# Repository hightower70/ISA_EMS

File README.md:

# 2MByte ISA EMS Expansion Card for IBM PC XT computers

This is a redesign of the **lo-tech.co.uk** [2Mb ISA EMS board](https://www.lo-tech.co.uk/wiki/Lo-tech_2MB_EMS_Board) with some changes:

- All thru-hole instead of SMD, while retaining a rather compact format
- Simplified address decoding and storage circuits for less chip count

All design files and gerber files for PCB manufacturing are avaiable in the repository. The schematics [schematics](schematics.pdf) is also avaiable in PDF format.

The card was tested in modern replica of an XT computer like Xi8088 and Micro8088 without issues.

## Configuration

To configure the EMS, jumpers on J2 header are used.

Pins pairs 1 and 2 configure the Page Frame base address, while 3 and 4 configure the IO Port base address.

Page Frame Address:

| 1 | 2 | EMS Page Frame Base |
| - | - | ------------------- |
| X | X |        C000h        |
| - | X |        D000h        |
| X | - |        E000h        |
| - | - |       Invalid       |

Port Base Address

| 3 | 4 | EMS IO Port Base |
| - | - | ---------------- |
| X | X |     260-263h     |
| - | X |     264-267h     |
| X | - |     268-26Bh     |
| - | - |     26C-26Fh     |

 (-=no jumper (opened), X=jumper (closed))

## Usage

You need a **memory manager** to use this board. I'm including the `LTEMM` driver provided by lo-tech in this repository. Please refer to [this](https://www.lo-tech.co.uk/wiki/Terms_and_Conditions) page regarding the terms of use.

## Bill of Materials

All ICs are in DIP package.

- C1,C4 ,C5 ,C6, C7, C8, C9, C10, C11, C12: 100nF, ceramic
- C2, C3: 10uF / 50v electrolytic caps
- J2 2x4 2.5mm breakable header
- RN1: resistor network, 10k, bussed, 5 pins
- RN2: resistor network, 10k, bussed, 9 pins. 
- U1, U2, U3, U4: AS6C4008-55PCN (You don't need to fill all sockets: fit as much memory as you need starting from socket 1!)
- U5: 74LS139
- U6: 74LS245
- U7, U10: 74HCT688
- U8, U9: 74LS670
- ISA bracket: Keystone 9202, plus screws.

## Credits

- Thanks to [hkzab](https://github.com/hkzlab/ISA_EMS_2Mb) for publishing a similar design
- Thanks to [lo-tech.co.uk](https://www.lo-tech.co.uk/) for having published their schematics
- Thanks to [Sergey](http://www.malinov.com/Home/sergeys-projects) for all his projects!

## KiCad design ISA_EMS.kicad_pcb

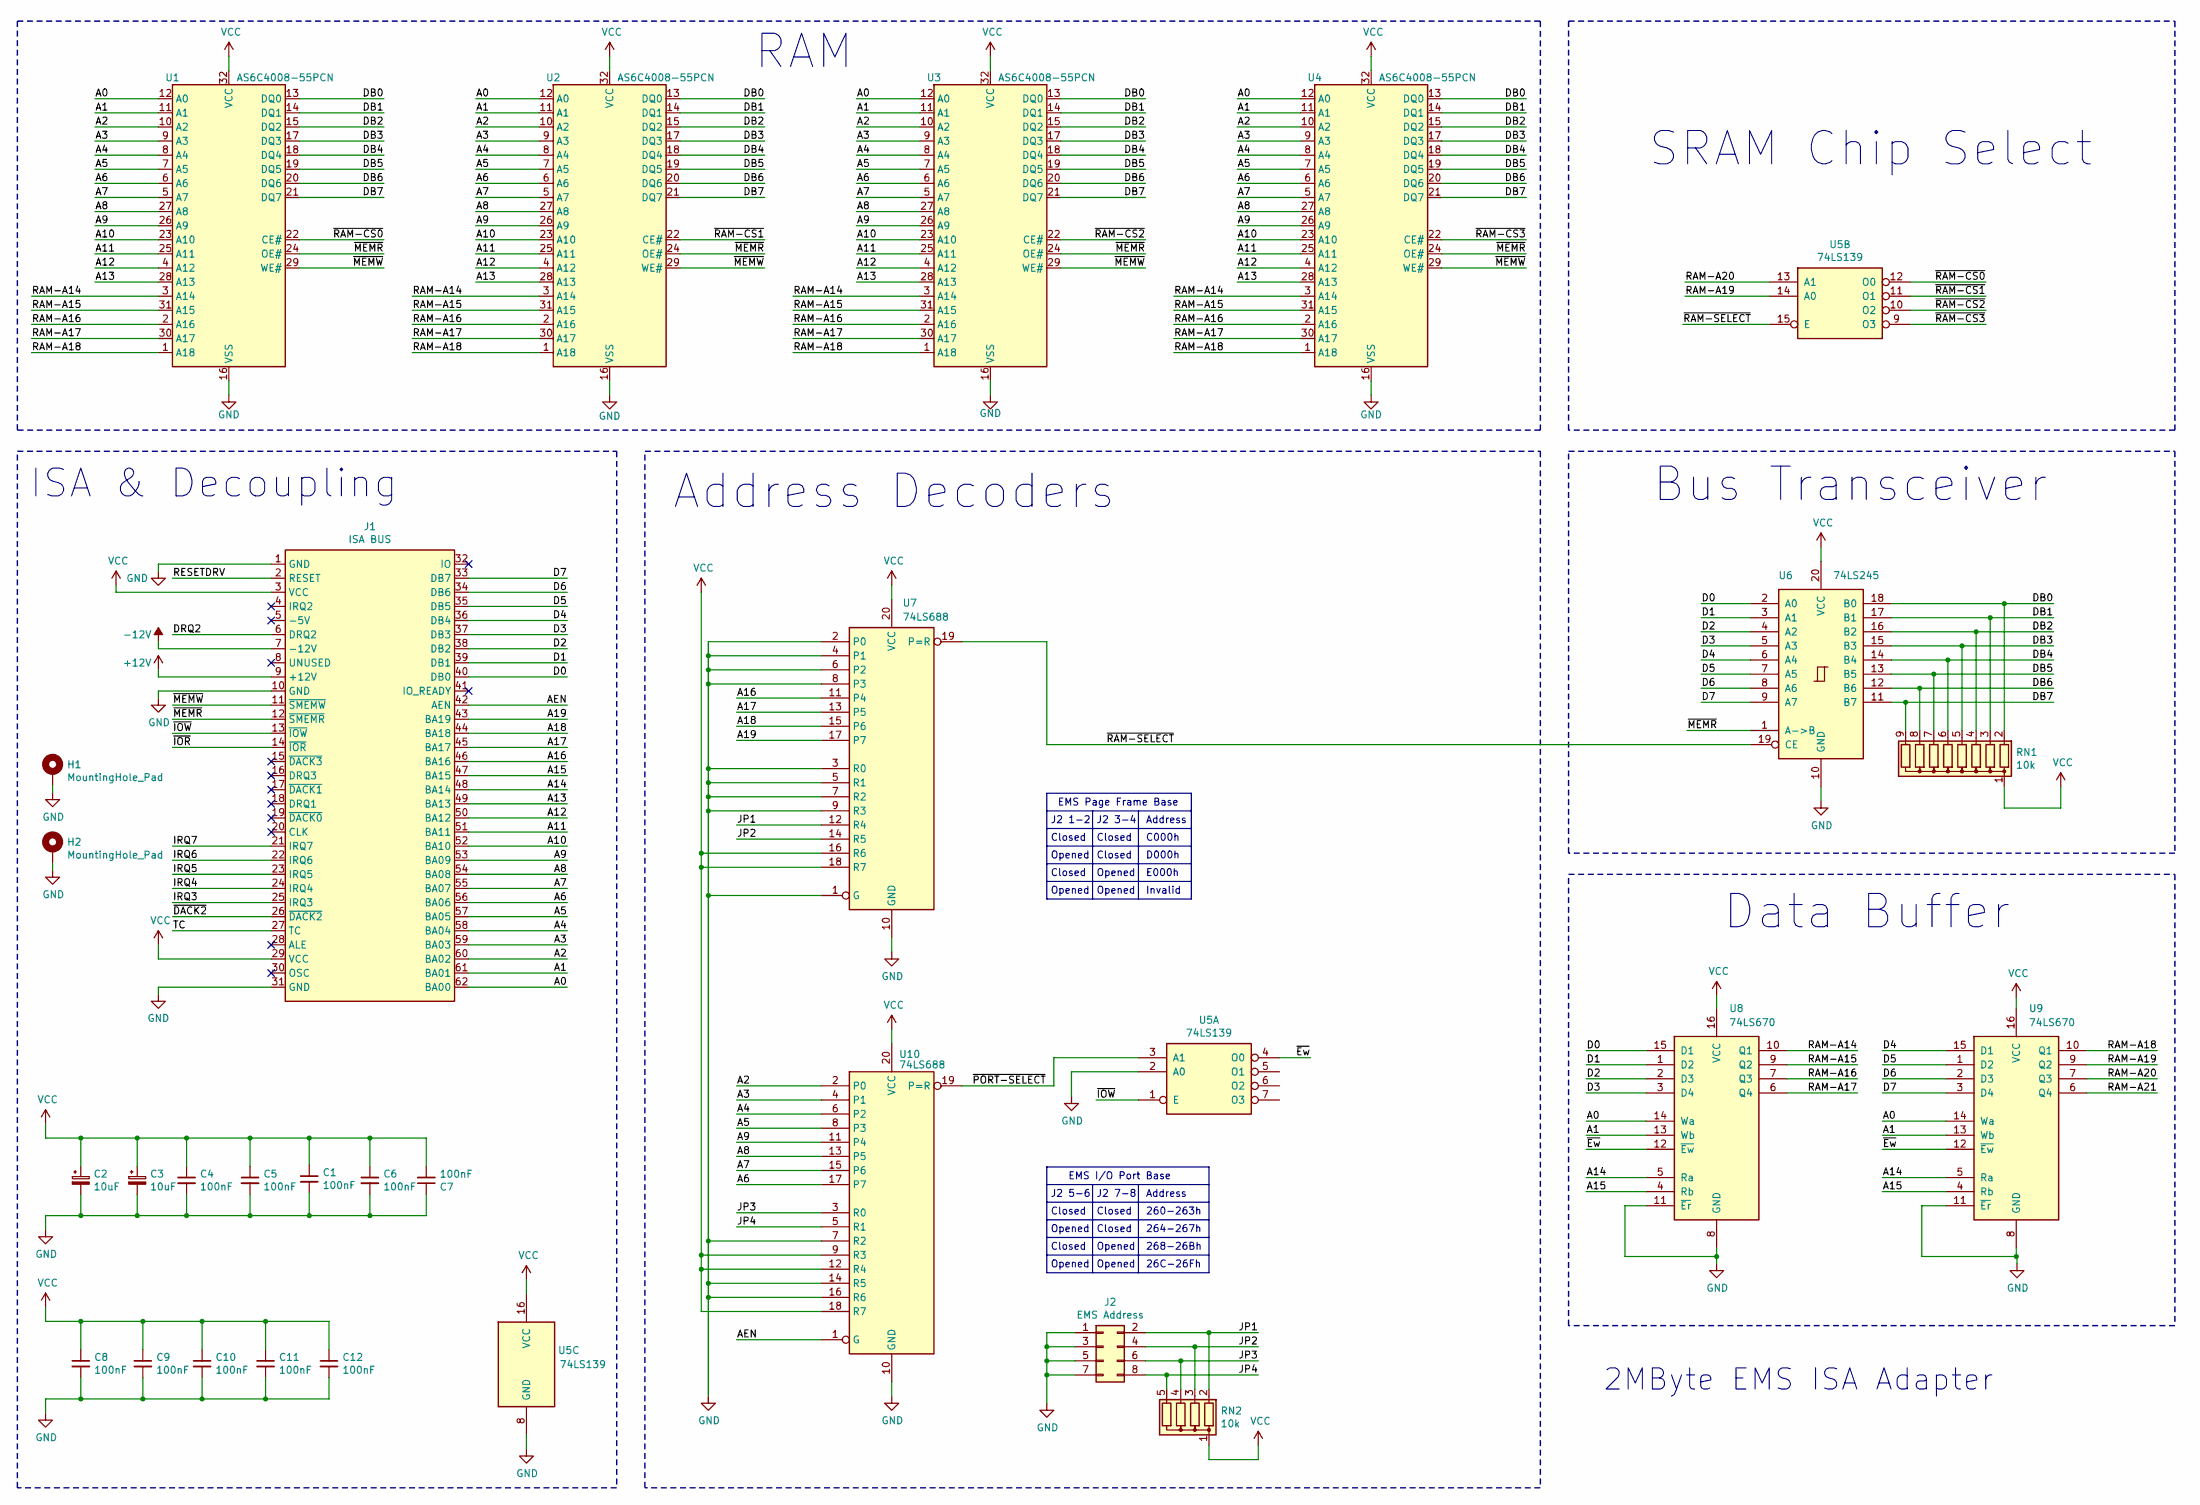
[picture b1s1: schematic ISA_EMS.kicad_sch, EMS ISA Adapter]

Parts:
C1, C4, C5, C6, C7, C8, C9, C10, C11, C12: 100nF; C_Disc_D6.0mm_W2.5mm_P5.00mm
C2, C3: 10uF; CP_Radial_D5.0mm_P2.50mm
H1: MountingHole_Pad; MountingHole_3mm_Pad
H2: MountingHole_Pad; MountingHole_3.5mm_Pad_TopBottom
J1: ISA BUS; BUS_XT
J2: EMS Address; PinHeader_2x04_P2.54mm_Vertical
RN1: 10k; R_Array_SIP9
RN2: 10k; R_Array_SIP5
U1, U2, U3, U4: AS6C4008-55PCN; DIP-32_W15.24mm
U5: 74LS139; DIP-16_W7.62mm
U6: 74LS245; DIP-20_W7.62mm
U7, U10: 74LS688; DIP-20_W7.62mm
U8, U9: 74LS670; DIP-16_W7.62mm

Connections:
+12V: J1.9 (+12V)
-12V: J1.7 (-12V)
/A0: J1.62 (BA00), U1.12 (A0), U2.12 (A0), U3.12 (A0), U4.12 (A0), U8.14 (Wa), U9.14 (Wa)
/A1: J1.61 (BA01), U1.11 (A1), U2.11 (A1), U3.11 (A1), U4.11 (A1), U8.13 (Wb), U9.13 (Wb)
/A2: J1.60 (BA02), U1.10 (A2), U2.10 (A2), U3.10 (A2), U4.10 (A2), U10.2 (P0)
/A3: J1.59 (BA03), U1.9 (A3), U2.9 (A3), U3.9 (A3), U4.9 (A3), U10.4 (P1)
/A4: J1.58 (BA04), U1.8 (A4), U2.8 (A4), U3.8 (A4), U4.8 (A4), U10.6 (P2)
/A5: J1.57 (BA05), U1.7 (A5), U2.7 (A5), U3.7 (A5), U4.7 (A5), U10.8 (P3)
/A6: J1.56 (BA06), U1.6 (A6), U2.6 (A6), U3.6 (A6), U4.6 (A6), U10.17 (P7)
/A7: J1.55 (BA07), U1.5 (A7), U2.5 (A7), U3.5 (A7), U4.5 (A7), U10.15 (P6)
/A8: J1.54 (BA08), U1.27 (A8), U2.27 (A8), U3.27 (A8), U4.27 (A8), U10.13 (P5)
/A9: J1.53 (BA09), U1.26 (A9), U2.26 (A9), U3.26 (A9), U4.26 (A9), U10.11 (P4)
/A10: J1.52 (BA10), U1.23 (A10), U2.23 (A10), U3.23 (A10), U4.23 (A10)
/A11: J1.51 (BA11), U1.25 (A11), U2.25 (A11), U3.25 (A11), U4.25 (A11)
/A12: J1.50 (BA12), U1.4 (A12), U2.4 (A12), U3.4 (A12), U4.4 (A12)
/A13: J1.49 (BA13), U1.28 (A13), U2.28 (A13), U3.28 (A13), U4.28 (A13)
/A14: J1.48 (BA14), U8.5 (Ra), U9.5 (Ra)
/A15: J1.47 (BA15), U8.4 (Rb), U9.4 (Rb)
/A16: J1.46 (BA16), U7.11 (P4)
/A17: J1.45 (BA17), U7.13 (P5)
/A18: J1.44 (BA18), U7.15 (P6)
/A19: J1.43 (BA19), U7.17 (P7)
/AEN: J1.42 (AEN), U10.1 (G)
/D0: J1.40 (DB0), U6.2 (A0), U8.15 (D1)
/D1: J1.39 (DB1), U6.3 (A1), U8.1 (D2)
/D2: J1.38 (DB2), U6.4 (A2), U8.2 (D3)
/D3: J1.37 (DB3), U6.5 (A3), U8.3 (D4)
/D4: J1.36 (DB4), U6.6 (A4), U9.15 (D1)
/D5: J1.35 (DB5), U6.7 (A5), U9.1 (D2)
/D6: J1.34 (DB6), U6.8 (A6), U9.2 (D3)
/D7: J1.33 (DB7), U6.9 (A7), U9.3 (D4)
/DB0: RN1.2 (R1), U1.13 (DQ0), U2.13 (DQ0), U3.13 (DQ0), U4.13 (DQ0), U6.18 (B0)
/DB1: RN1.3 (R2), U1.14 (DQ1), U2.14 (DQ1), U3.14 (DQ1), U4.14 (DQ1), U6.17 (B1)
/DB2: RN1.4 (R3), U1.15 (DQ2), U2.15 (DQ2), U3.15 (DQ2), U4.15 (DQ2), U6.16 (B2)
/DB3: RN1.5 (R4), U1.17 (DQ3), U2.17 (DQ3), U3.17 (DQ3), U4.17 (DQ3), U6.15 (B3)
/DB4: RN1.6 (R5), U1.18 (DQ4), U2.18 (DQ4), U3.18 (DQ4), U4.18 (DQ4), U6.14 (B4)
/DB5: RN1.7 (R6), U1.19 (DQ5), U2.19 (DQ5), U3.19 (DQ5), U4.19 (DQ5), U6.13 (B5)
/DB6: RN1.8 (R7), U1.20 (DQ6), U2.20 (DQ6), U3.20 (DQ6), U4.20 (DQ6), U6.12 (B6)
/DB7: RN1.9 (R8), U1.21 (DQ7), U2.21 (DQ7), U3.21 (DQ7), U4.21 (DQ7), U6.11 (B7)
/DRQ2: J1.6 (DRQ2)
/IRQ3: J1.25 (IRQ3)
/IRQ4: J1.24 (IRQ4)
/IRQ5: J1.23 (IRQ5)
/IRQ6: J1.22 (IRQ6)
/IRQ7: J1.21 (IRQ7)
/JP1: J2.2, RN2.2 (R1), U7.12 (R4)
/JP2: J2.4, RN2.3 (R2), U7.14 (R5)
/JP3: J2.6, RN2.4 (R3), U10.3 (R0)
/JP4: J2.8, RN2.5 (R4), U10.5 (R1)
/RAM-A14: U1.3 (A14), U2.3 (A14), U3.3 (A14), U4.3 (A14), U8.10 (Q1)
/RAM-A15: U1.31 (A15), U2.31 (A15), U3.31 (A15), U4.31 (A15), U8.9 (Q2)
/RAM-A16: U1.2 (A16), U2.2 (A16), U3.2 (A16), U4.2 (A16), U8.7 (Q3)
/RAM-A17: U1.30 (A17), U2.30 (A17), U3.30 (A17), U4.30 (A17), U8.6 (Q4)
/RAM-A18: U1.1 (A18), U2.1 (A18), U3.1 (A18), U4.1 (A18), U9.10 (Q1)
/RAM-A19: U5.14 (A0), U9.9 (Q2)
/RAM-A20: U5.13 (A1), U9.7 (Q3)
/RAM-A21: U9.6 (Q4)
/RESETDRV: J1.2 (RESET)
/TC: J1.27 (TC)
/~DACK2: J1.26 (~DACK2)
/~Ew: U5.4 (O0), U8.12 (~Ew), U9.12 (~Ew)
/~IOR: J1.14 (~IOR)
/~IOW: J1.13 (~IOW), U5.1 (E)
/~MEMR: J1.12 (~SMEMR), U1.24 (OE#), U2.24 (OE#), U3.24 (OE#), U4.24 (OE#), U6.1 (A->B)
/~MEMW: J1.11 (~SMEMW), U1.29 (WE#), U2.29 (WE#), U3.29 (WE#), U4.29 (WE#)
/~PORT-SELECT: U5.3 (A1), U10.19 (P=R)
/~RAM-CS0: U1.22 (CE#), U5.12 (O0)
/~RAM-CS1: U2.22 (CE#), U5.11 (O1)
/~RAM-CS2: U3.22 (CE#), U5.10 (O2)
/~RAM-CS3: U4.22 (CE#), U5.9 (O3)
/~RAM-SELECT: U5.15 (E), U6.19 (CE), U7.19 (P=R)
GND: C1.2, C2.2, C3.2, C4.2, C5.2, C6.2, C7.1, C8.2, C9.2, C10.2, C11.2, C12.2, H1.1, H2.1, J1.1 (GND), J1.10 (GND), J1.31 (GND), J2.1, J2.3, J2.5, J2.7, U1.16 (VSS), U2.16 (VSS), U3.16 (VSS), U4.16 (VSS), U5.2 (A0), U5.8 (GND), U6.10 (GND), U7.1 (G), U7.2 (P0), U7.3 (R0), U7.4 (P1), U7.5 (R1), U7.6 (P2), U7.7 (R2), U7.8 (P3), U7.9 (R3), U7.10 (GND), U8.8 (GND), U8.11 (~Er), U9.8 (GND), U9.11 (~Er), U10.7 (R2), U10.10 (GND), U10.14 (R5), U10.16 (R6)
VCC: C1.1, C2.1, C3.1, C4.1, C5.1, C6.1, C7.2, C8.1, C9.1, C10.1, C11.1, C12.1, J1.3 (VCC), J1.29 (VCC), RN1.1 (common), RN2.1 (common), U1.32 (VCC), U2.32 (VCC), U3.32 (VCC), U4.32 (VCC), U5.16 (VCC), U6.20 (VCC), U7.16 (R6), U7.18 (R7), U7.20 (VCC), U8.16 (VCC), U9.16 (VCC), U10.9 (R3), U10.12 (R4), U10.18 (R7), U10.20 (VCC)

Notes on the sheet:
Closed
C000h
J2 5-6
26C-26Fh
2MByte EMS ISA Adapter
D000h
SRAM Chip Select
Bus Transceiver
EMS Page Frame Base
Invalid
EMS I/O Port Base
Address
Address Decoders
264-267h
J2 7-8
Opened
Data Buffer
ISA & Decoupling
J2 3-4
268-26Bh
RAM
E000h
J2 1-2
260-263h

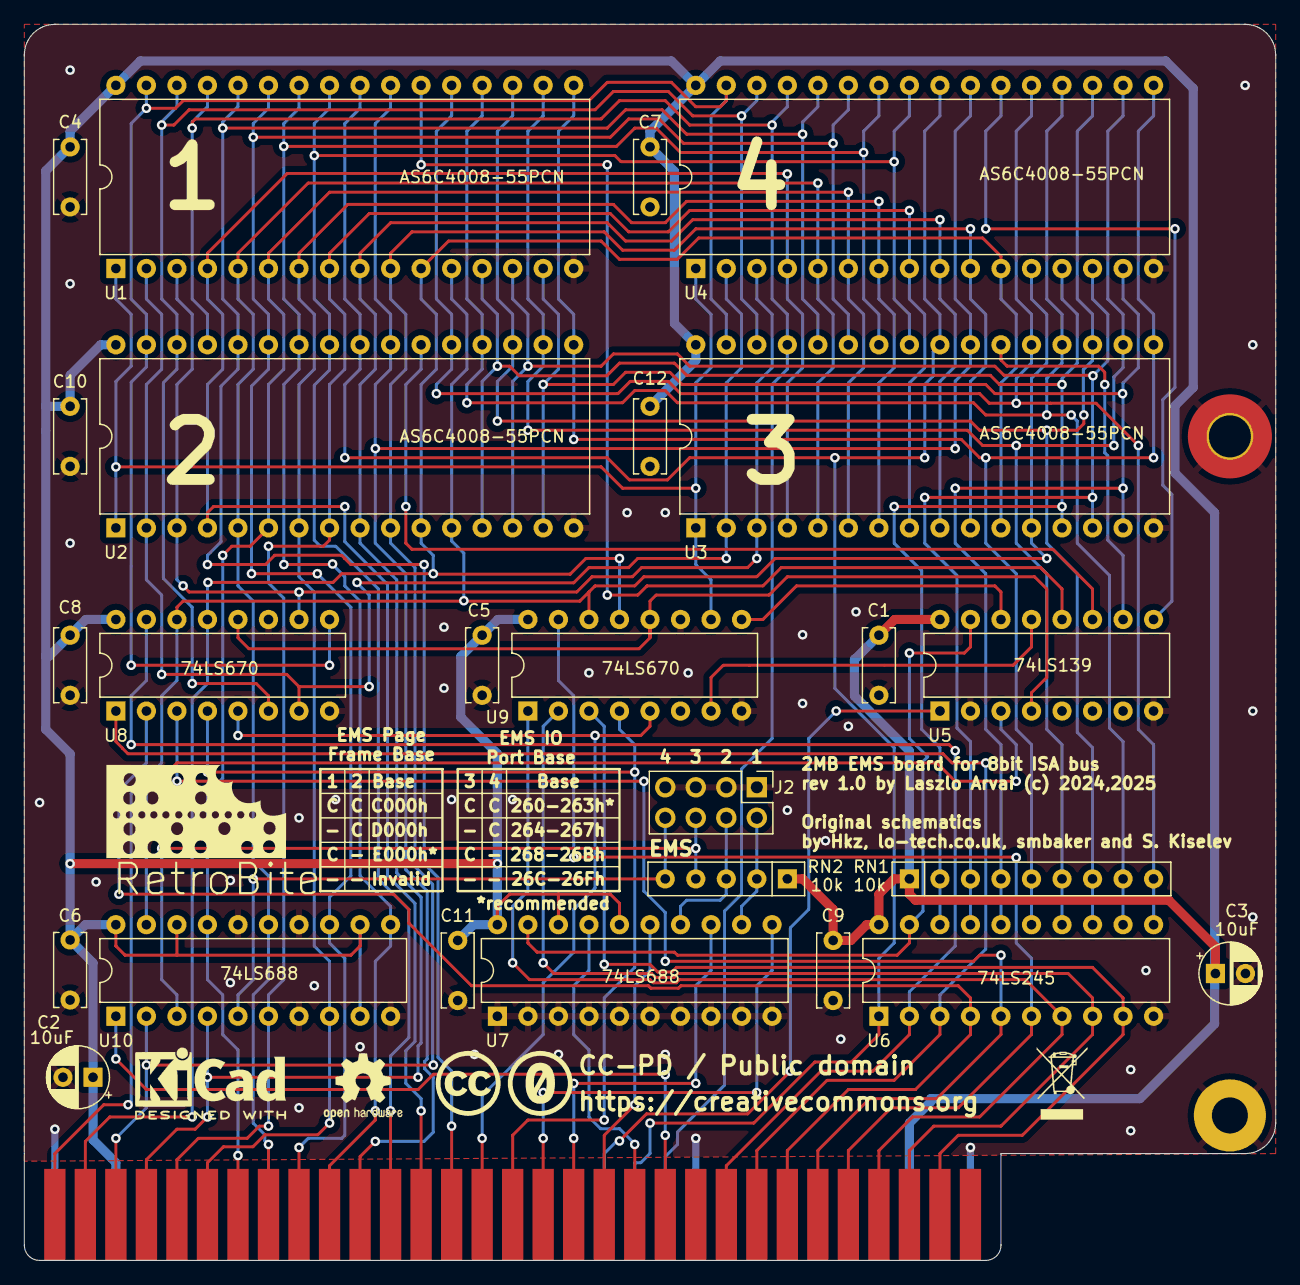
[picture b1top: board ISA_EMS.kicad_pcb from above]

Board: 2 copper layers, 104.1 x 102.9 mm, 28 parts (0 on the bottom side), 60 nets.

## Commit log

2025-01-29 Gerber files has been added
2025-01-29 Schematics has been added
2025-01-29 PCB update

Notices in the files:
ISA_EMS.kicad_pcb:
rev 1.0 by Laszlo Arvai (c) 2024,2025
parts and their libraries:
CC-PD / Public domain
